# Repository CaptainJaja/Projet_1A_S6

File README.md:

# 🚀 Projet 1A S6 - Robot Bluetooth + Odometrie

Ce projet consiste à concevoir un robot télécommandé via Bluetooth grâce à une application Android, avec odométrie, détection d'obstacles, et supervision ROS.

---

## 📌 Cahier des charges

### 🔹 Robot
- Communication **UART** avec le module **Bluetooth HC-05**  
- **Contrôle de deux moteurs DC à encodeurs** via un driver **TB6612FNG**  
- **Lecture des encodeurs** pour faire de l'**odométrie**  
- **Connexion à une Raspberry Pi** pour supervision et traitement via **ROS**  
- **Détection d'obstacle** via un capteur **ultrason HC-SR04**  
- **Module infrarouge** pour détection de ligne ou d'obstacles courts  
- **Affichage LED** pour état du robot ou esthétique  
- **Commande de deux servo-moteurs** pour actionner des éléments  

### 🔹 Application Android
- Interface graphique avec **boutons de commande**  
- **Connexion Bluetooth** pour envoyer des commandes au robot  

---

## ⚙️ Matériel utilisé

| Composant | Référence | Rôle |
|-----------|-----------|-----------|
| **Microcontrôleur** | STM32 (modèle à préciser) | Gestion des moteurs, capteurs, servo et communication Bluetooth |
| **Module Bluetooth** | HC-06 / HC-05 | Communication avec l’application Android |
| **Moteurs DC à encodeur** | GA12-N20 + encodeur magnétique | Déplacement du robot + odométrie |
| **Driver moteur** | TB6612FNG | Pilotage des moteurs |
| **Batterie** | LiPo 7.4V (capacité à préciser) | Alimentation du système |
| **Régulateurs de tension** | 7.4V → 5V (R-78B5.0-2.0), 5V → 3.3V (BU33SD5WG-TR)| Alimentation des composants |
| **Capteur ultrason** | HC-SR04 | Détection d'obstacles |
| **Module infrarouge** | (modèle à préciser) | Détection de ligne ou d'obstacle proche |
| **Servomoteurs** | (modèle à préciser) x2 | Actionneurs divers |
| **LEDs** | 2x minimum | Indicateurs visuels |
| **Raspberry Pi** | (modèle à préciser) | Exécution de ROS et traitement haut niveau |

---

## 🛠 Architecture du PCB

Notre projet comporte **deux versions de PCB** :

### V1 : Prototype de base
- Connecteurs moteurs, servo, HC-SR04, HC-05 ; Driver ; STM
- Pas d'encodeur, ni module infrarouge, ni connecteurs pour la Raspberry Pi

### V2 : Version finale
- Connecteurs pour les **encodeurs**, la **Raspberry Pi**, et le **module infrarouge** ajoutés
- Circuits d'alimentation optimisés pour alimentation partagée

---

## ⏳ Tableau d'avancement du projet

| Séance | Avancement                                                                                                                                                                                                           |
|--------|----------------------------------------------------------------------------------------------------------------------------------------------------------------------------------------------------------------------|
| Séance 1 | Répartition des tâches (modélisation 3D / code + PCB / appli Android), choix des composants                                                                                                                          |
| Séance 2 | - Début du PCB V1 (sans encodeur, Raspberry, infrarouge) <br>- Début application Android <br>- Début modélisation mécanique                                                                                          |
| Séance 3 | - Finalisation du PCB V1 <br>- 1ère version de l'application (nombreuses fonctionnalités manquantes)<br>-la conception 3D continue d'avancer                                                                         |
| Séance 4 | - Début des tests du **module HC-05** <br>- Implémentation des fonctionnalités mais beaucoup d'erreurs <br>-changement des dimensions de la structure 3D car changement d'agencement des éléments dans le robot |
| Séance 5 | Finalisation de la **commande à distance** (prototype robot avec HC-05)<br>-la conception 3D continue d'avancer                                                                                                      |
| Séance 6 | - Début du PCB V2 (ajout Raspberry, encodeurs, infrarouge) <br>- Plus d'erreurs grâce aux bonnes permissions demandées <br>- début de l'impression 3D                                                                |
| Séance 7 | Finalisation du modèle du PCB V2, **commande des composants et du PCB** <br>-fin de l'impression 3D                                                                                                                  |
| Séance 8 | Finalisation du modèle 3D, montage PCB et robot prototype, test |
| Séance 9 | Corrections et impressions 3D, montage du robot final |
---

## 📋 Répartition des tâches

| Nom | Tâche principale                                                                                                                                                       |
|-----------|------------------------------------------------------------------------------------------------------------------------------------------------------------------------|
| **CAPODAGI Janus** | Conception PCB (https://github.com/CaptainJaja/Projet_1A_S6/tree/main/Hardware/PCB),  code STM32 (https://github.com/CaptainJaja/Projet_1A_S6/tree/main/Software/Code) |
| **BUI HAI Christophe** | Développement de l’application Android (https://github.com/CaptainJaja/Projet_1A_S6/tree/main/Application)                                                             |
| **MILLON Raphaëlle** | Conception mécanique du robot :modélisation 3D, intégration Raspberry (https://github.com/CaptainJaja/Projet_1A_S6/tree/main/Hardware/3D)                              |

---

## 📝 Remarques et pistes d'amélioration

- Ajouter un schéma de l'architecture du système (STM32 + Raspberry + ROS)
- Tester la communication entre STM32 et Raspberry via UART 

---

Ce README est susceptible d'être mis à jour au fur et à mesure de l'avancement du projet. 🚀

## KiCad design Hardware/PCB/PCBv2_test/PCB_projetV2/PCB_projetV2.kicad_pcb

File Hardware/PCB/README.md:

# 🚀 Robot PCB - STM32 + HC-05 + Motor Driver  

Ce projet est un PCB conçu pour contrôler un robot suiveur de ligne avec obstacle, utilisant un **STM32L552CCTx** et un module **Bluetooth HC-05** pour la communication. Il comprend un **driver moteur TB6612FNG**, plusieurs GPIO et connecteurs pour capteurs.

## 📸 Aperçu du PCB version 1 (moteur sans encodeur, pas de connexion raspberry)
### **Face Avant**

### **Face Arrière**

## 📸 Aperçu du PCB version 2 (+moteur avec encodeur, +connexion raspberry (UART), +Module infrarouge)
### **Face Avant**

### **Face Arrière**

## 📦 Composants intégrés (version finale : V2)
- **Microcontrôleur :** STM32L552CCTx
- **Communication (PinHeader 01x04) :** HC-05 (Bluetooth, connecté en UART au MCU)
- **Contrôle des moteurs :** TB6612FNG (Driver moteur DC)
- **Indicateur d'état Bluetooth :** LED
- **Interface GPIO :** Rangée **3x4 pinheader** (GPIO-3.3V-GND)
- **Connectique :**
  - 2x **Connecteurs JST 01x03** pour servomoteurs
  - 2x **Connecteurs JST 01x06** pour moteurs DC
  - 1x **Connecteur JST 01x06** pour module infrarouge
  - 1x **Connecteur JST 01x02** pour alimentation
  - 1x **Connecteur ST-LINK** pour programmation/debug
  - 1x **Connecteur PinHeader 01x02** pour connexion UART avec raspberry
  - 1x **Connecteur PinHeader 02x03** pour connexion avec les LEDs
  - 1x **Connecteur PinHeader 01x02** pour connecter les masses STM/Raspberry
- **Alimentation :**
  - **Régulateur 7.5V → 5V**
  - **Régulateur 5V → 3.3V**
- **Boutons poussoirs :**
  - **Reset du MCU**
- **Passifs :** Condensateurs de découplage, bobine, résistances (**SMD**)

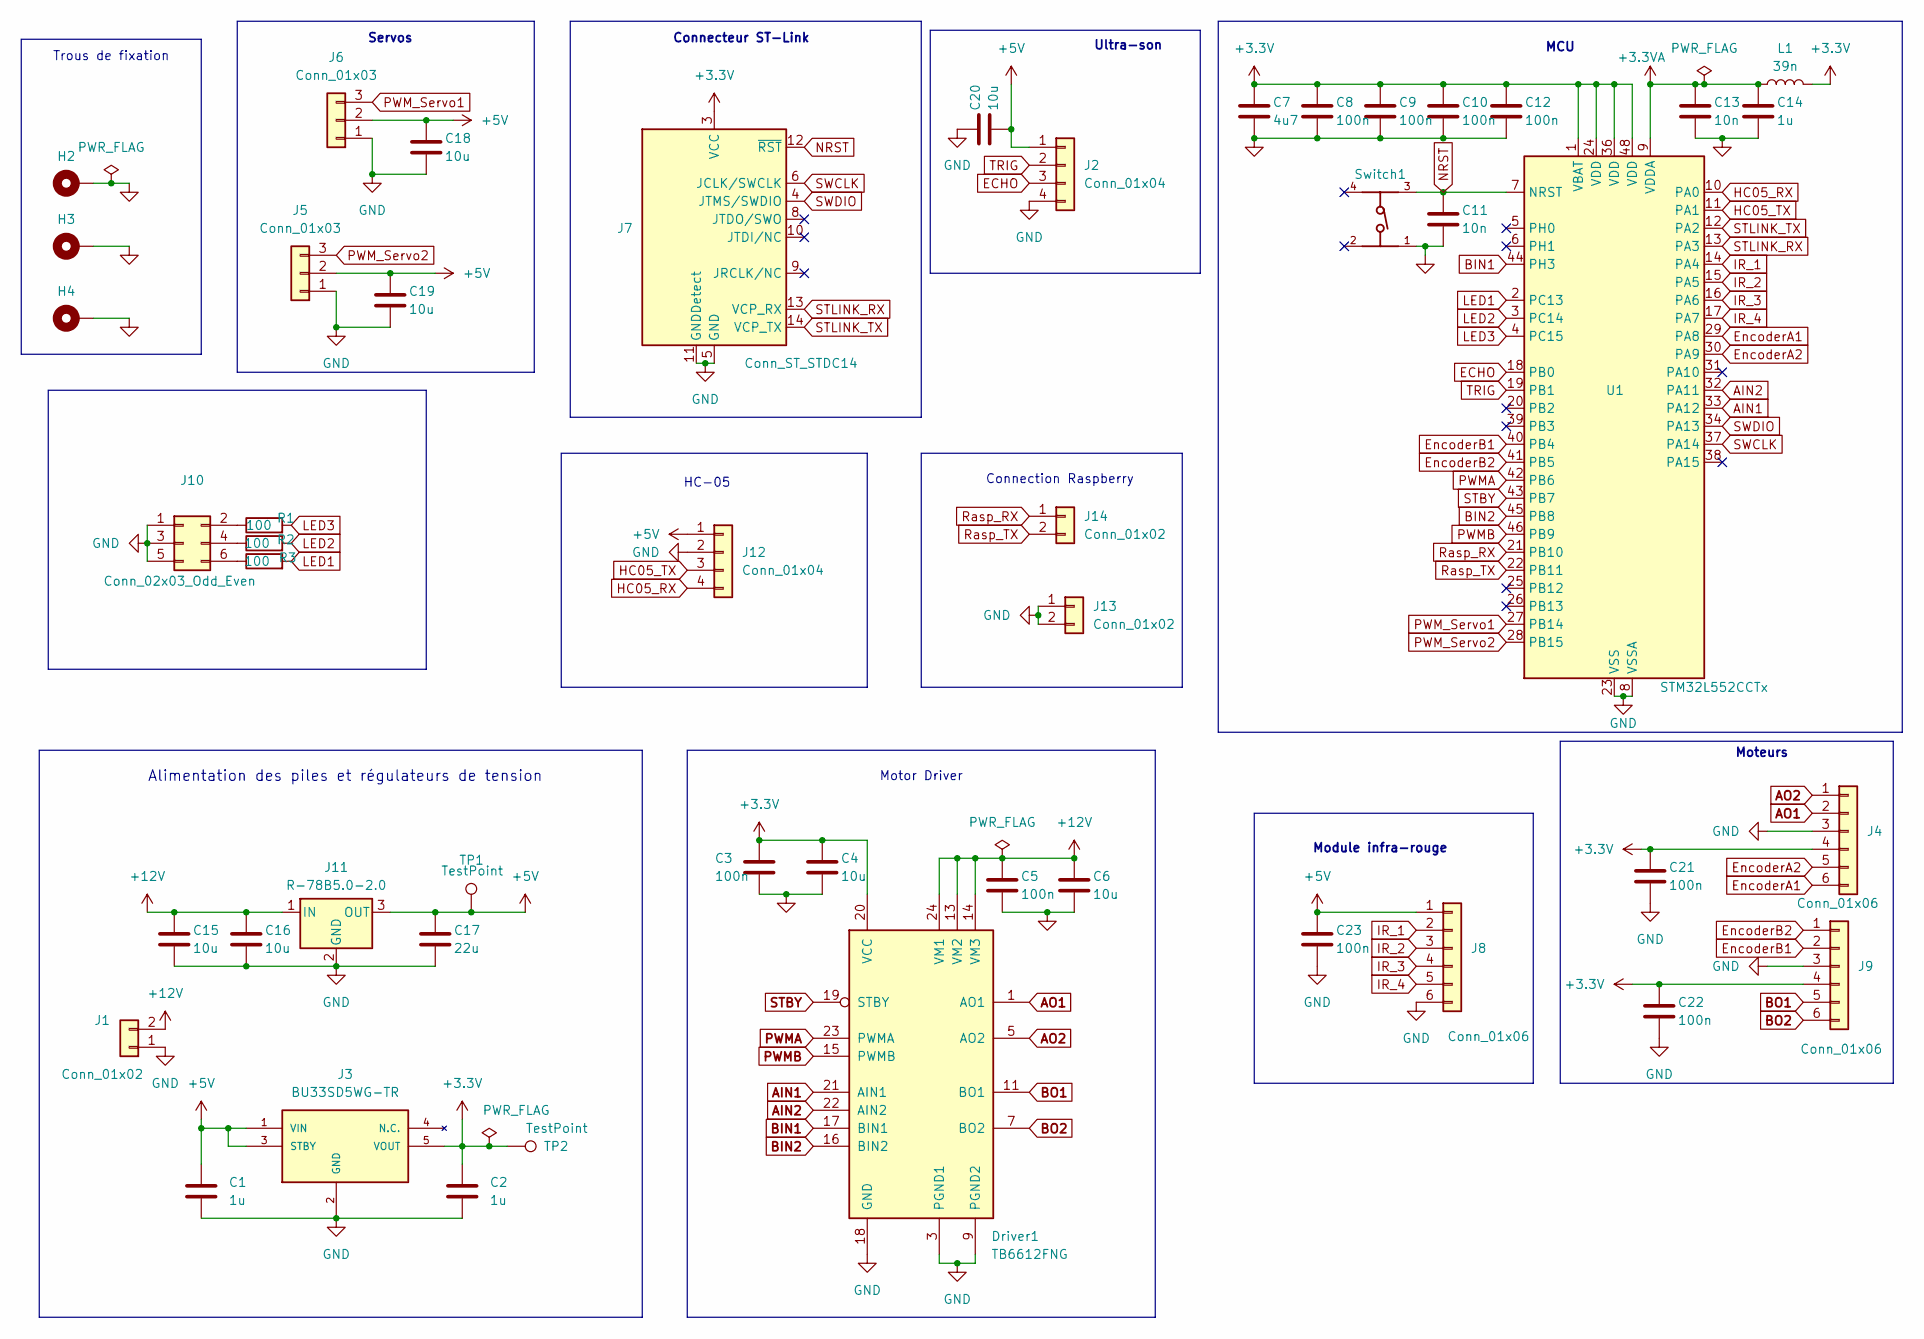
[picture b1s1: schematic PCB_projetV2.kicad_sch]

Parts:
C1, C2: 1u; C_0603_1608Metric_Pad1.08x0.95mm_HandSolder
C3, C5, C8, C9, C10, C12, C21, C22, C23: 100n; C_0402_1005Metric
C4, C6, C15, C16, C18, C19, C20: 10u; C_0603_1608Metric
C7: 4u7; C_0603_1608Metric
C11, C13: 10n; C_0402_1005Metric
C14: 1u; C_0402_1005Metric
C17: 22u; C_0805_2012Metric
Driver1: TB6612FNG; SSOP-24_5.3x8.2mm_P0.65mm
H2, H3, H4: MountingHole_Pad; MountingHole_2.7mm_M2.5_Pad
J1: Conn_01x02; JST_XH_S2B-XH-A-1_1x02_P2.50mm_Horizontal
J2: Conn_01x04; JST_PH_B4B-PH-K_1x04_P2.00mm_Vertical
J3: BU33SD5WG-TR; SOT95P280X125-5N; Mouser_Part_Number 755-BU33SD5WG-TR
J4, J9: Conn_01x06; JST_XH_B6B-XH-A_1x06_P2.50mm_Vertical
J5, J6: Conn_01x03; JST_PH_B3B-PH-K_1x03_P2.00mm_Vertical
J7: Conn_ST_STDC14; PinHeader_2x07_P1.27mm_Vertical_SMD
J8: Conn_01x06; JST_XH_S6B-XH-A-1_1x06_P2.50mm_Horizontal
J10: Conn_02x03_Odd_Even; PinSocket_2x03_P2.54mm_Vertical
J11: R-78B5.0-2.0; Converter_DCDC_RECOM_R-78B-2.0_THT
J12: Conn_01x04; PinHeader_1x04_P2.54mm_Vertical
J13: Conn_01x02; PinHeader_1x02_P2.54mm_Vertical
J14: Conn_01x02; JST_EH_B2B-EH-A_1x02_P2.50mm_Vertical
L1: 39n; L_0603_1608Metric
R1, R2, R3: 100; R_0603_1608Metric
Switch1: 430471025826; PART-NUMBER 430471025826
TP1, TP2: TestPoint; TestPoint_Pad_D2.0mm
U1: STM32L552CCTx; LQFP-48_7x7mm_P0.5mm

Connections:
+3.3V: C2.1, C3.1, C4.1, C7.1, C8.1, C9.1, C10.1, C12.1, C21.1, C22.1, Driver1.20 (VCC), J3.5 (VOUT), J4.4, J7.3 (VCC), J9.4, L1.2, TP2.1, U1.1 (VBAT), U1.24 (VDD), U1.36 (VDD), U1.48 (VDD)
+3.3VA: C13.1, C14.1, L1.1, U1.9 (VDDA)
+5V: C1.1, C17.1, C18.1, C19.1, C20.2, C23.1, J2.1, J3.1 (VIN), J3.3 (STBY), J5.2, J6.2, J8.1, J11.3 (OUT), J12.1, TP1.1
+12V: C5.1, C6.1, C15.1, C16.1, Driver1.13 (VM2), Driver1.14 (VM3), Driver1.24 (VM1), J1.2, J11.1 (IN)
AIN1: Driver1.21 (AIN1), U1.33 (PA12)
AIN2: Driver1.22 (AIN2), U1.32 (PA11)
AO1: Driver1.1 (AO1), Driver1.2 (AO1), J4.2
AO2: Driver1.5 (AO2), Driver1.6 (AO2), J4.1
BIN1: Driver1.17 (BIN1), U1.44 (PH3)
BIN2: Driver1.16 (BIN2), U1.45 (PB8)
BO1: Driver1.11 (BO1), Driver1.12 (BO1), J9.5
BO2: Driver1.7 (BO2), Driver1.8 (BO2), J9.6
ECHO: J2.3, U1.18 (PB0)
EncoderA1: J4.6, U1.29 (PA8)
EncoderA2: J4.5, U1.30 (PA9)
EncoderB1: J9.2, U1.40 (PB4)
EncoderB2: J9.1, U1.41 (PB5)
GND: C1.2, C2.2, C3.2, C4.2, C5.2, C6.2, C7.2, C8.2, C9.2, C10.2, C11.2, C12.2, C13.2, C14.2, C15.2, C16.2, C17.2, C18.2, C19.2, C20.1, C21.2, C22.2, C23.2, Driver1.3 (PGND1), Driver1.4 (PGND1), Driver1.9 (PGND2), Driver1.10 (PGND2), Driver1.18 (GND), H2.1, H3.1, H4.1, J1.1, J2.4, J3.2 (GND), J4.3, J5.1, J6.1, J7.5 (GND), J7.7 (GND), J7.11 (GNDDetect), J8.6, J9.3, J10.1, J10.3, J10.5, J11.2 (GND), J12.2, J13.1, J13.2, Switch1.1, U1.8 (VSSA), U1.23 (VSS), U1.35 (VSS), U1.47 (VSS)
HC05_RX: J12.4, U1.10 (PA0)
HC05_TX: J12.3, U1.11 (PA1)
IR_1: J8.2, U1.14 (PA4)
IR_2: J8.3, U1.15 (PA5)
IR_3: J8.4, U1.16 (PA6)
IR_4: J8.5, U1.17 (PA7)
LED1: R3.2, U1.2 (PC13)
LED2: R2.2, U1.3 (PC14)
LED3: R1.2, U1.4 (PC15)
NRST: C11.1, J7.12 (~RST), Switch1.3, U1.7 (NRST)
unnamed: J10.2, R1.1
unnamed: J10.4, R2.1
unnamed: J10.6, R3.1
PWMA: Driver1.23 (PWMA), U1.42 (PB6)
PWMB: Driver1.15 (PWMB), U1.46 (PB9)
PWM_Servo1: J6.3, U1.27 (PB14)
PWM_Servo2: J5.3, U1.28 (PB15)
Rasp_RX: J14.1, U1.21 (PB10)
Rasp_TX: J14.2, U1.22 (PB11)
STBY: Driver1.19 (STBY), U1.43 (PB7)
STLINK_RX: J7.13 (VCP_RX), U1.13 (PA3)
STLINK_TX: J7.14 (VCP_TX), U1.12 (PA2)
SWCLK: J7.6 (JCLK/SWCLK), U1.37 (PA14)
SWDIO: J7.4 (JTMS/SWDIO), U1.34 (PA13)
TRIG: J2.2, U1.19 (PB1)

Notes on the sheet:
Module infra-rouge
Alimentation des piles et régulateurs de tension
Trous de fixation
Connection Raspberry
HC-05
Moteurs
Servos
Motor Driver
MCU
Ultra-son
Connecteur ST-Link

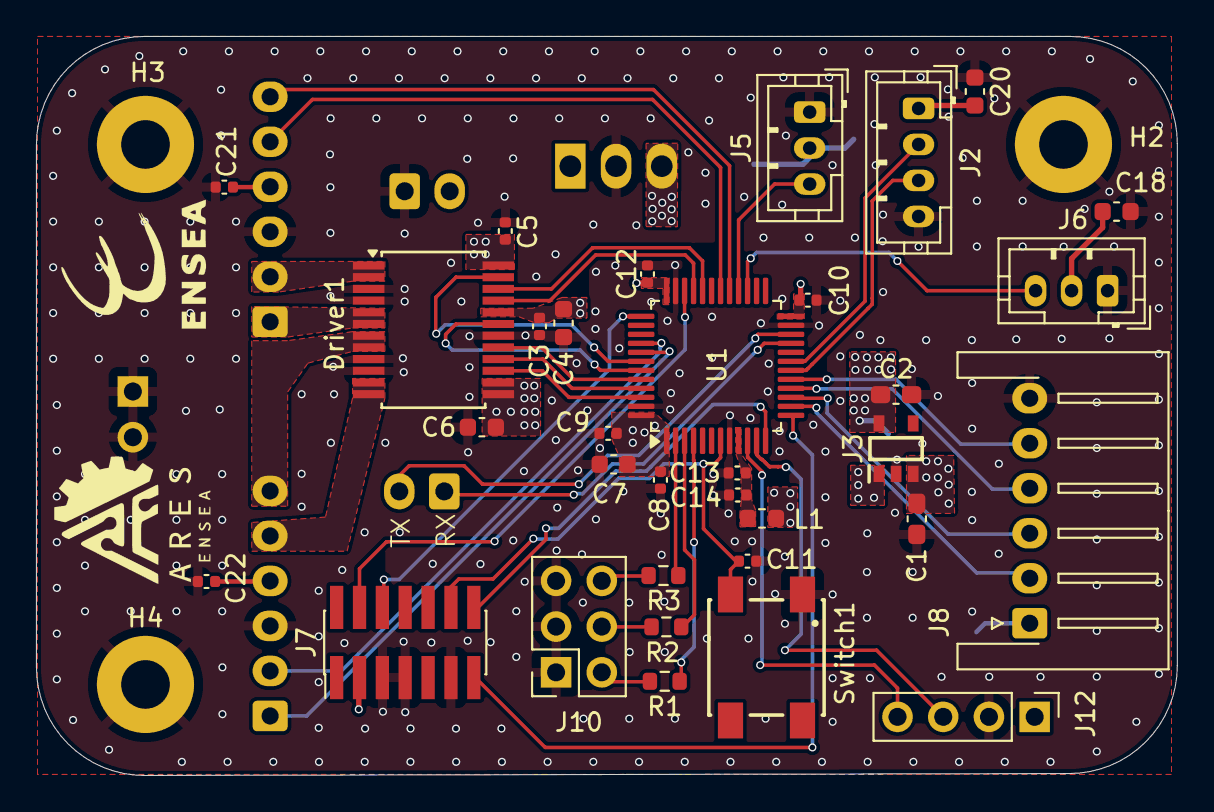
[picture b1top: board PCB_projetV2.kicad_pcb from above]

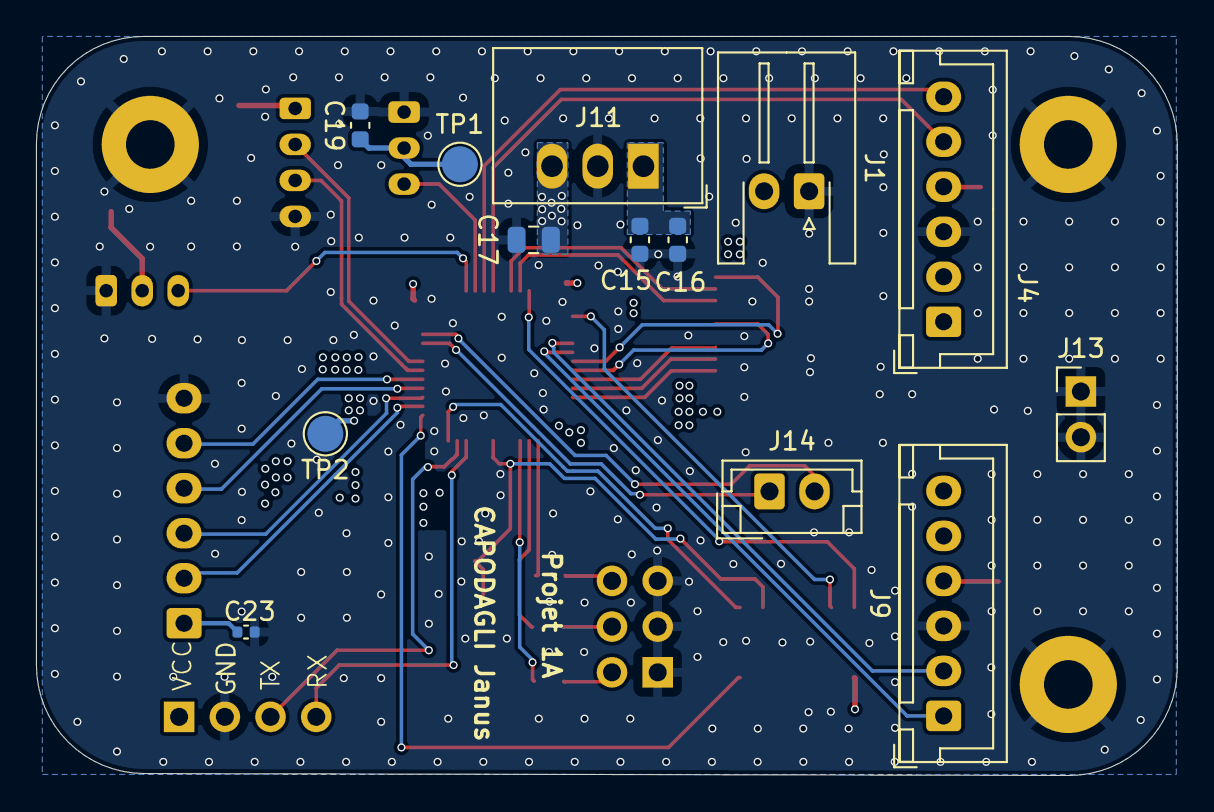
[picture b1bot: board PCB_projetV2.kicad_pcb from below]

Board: 4 copper layers, 63.4 x 41.1 mm, 49 parts (13 on the bottom side), 43 nets.

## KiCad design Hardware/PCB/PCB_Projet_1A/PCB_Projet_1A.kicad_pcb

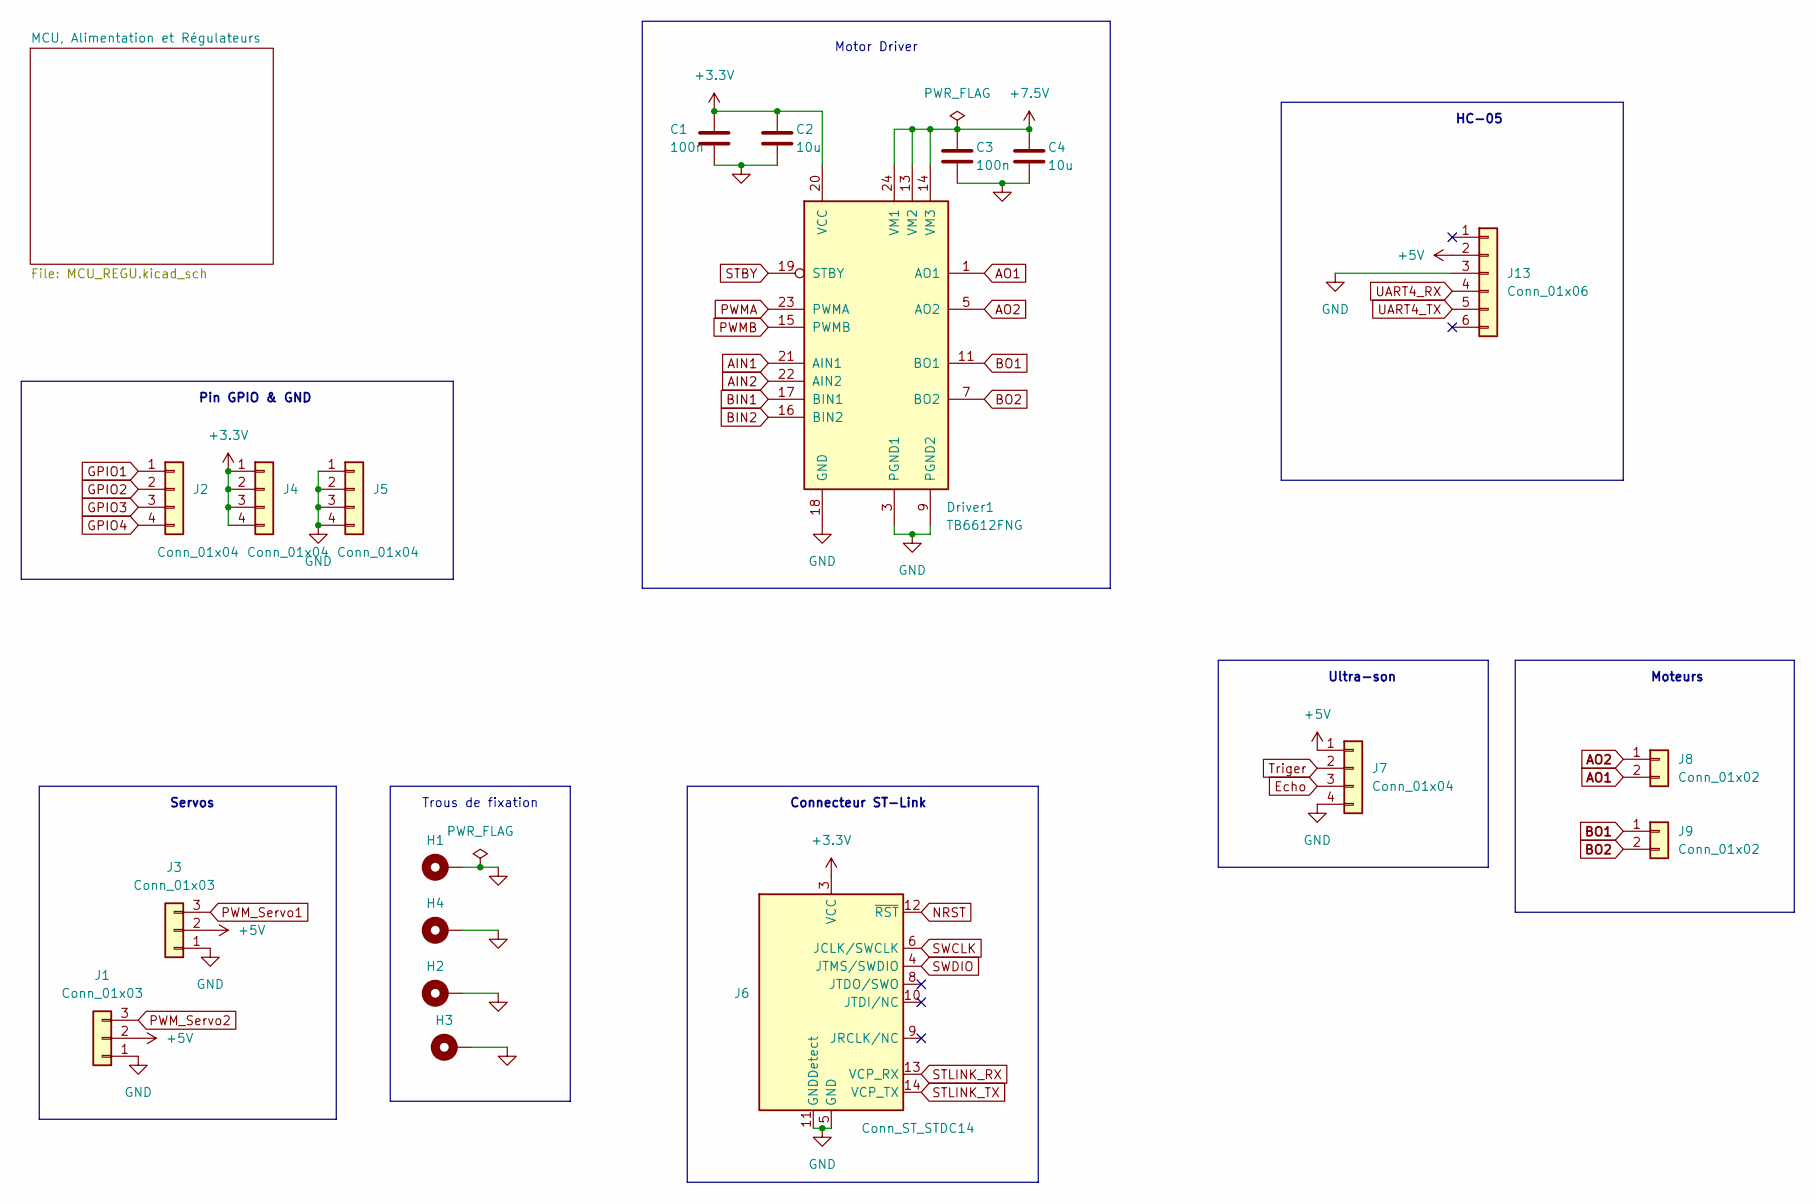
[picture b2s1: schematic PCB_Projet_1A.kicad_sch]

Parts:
C1, C3: 100n; C_0402_1005Metric
C2, C4: 10u; C_0805_2012Metric
Driver1: TB6612FNG; SSOP-24_5.3x8.2mm_P0.65mm
H1, H2, H3, H4: MountingHole_Pad; MountingHole_2.7mm_M2.5_Pad
J1, J3: Conn_01x03; JST_XH_B3B-XH-A_1x03_P2.50mm_Vertical
J2, J4, J5: Conn_01x04; PinHeader_1x04_P2.54mm_Vertical
J6: Conn_ST_STDC14; PinHeader_2x07_P1.27mm_Vertical_SMD
J7: Conn_01x04; JST_PH_B4B-PH-K_1x04_P2.00mm_Vertical
J8, J9: Conn_01x02; JST_XH_B2B-XH-A_1x02_P2.50mm_Vertical
J13: Conn_01x06; PinHeader_1x06_P2.54mm_Vertical

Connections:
+3.3V: C1.1, C2.1, Driver1.20 (VCC), J4.1, J4.2, J4.3, J4.4, J6.3 (VCC); also elsewhere on the board
+5V: J1.2, J3.2, J7.1, J13.2; also elsewhere on the board
+7.5V: C3.1, C4.1, Driver1.13 (VM2), Driver1.14 (VM3), Driver1.24 (VM1); also elsewhere on the board
AIN1: Driver1.21 (AIN1); also elsewhere on the board
AIN2: Driver1.22 (AIN2); also elsewhere on the board
AO1: Driver1.1 (AO1), Driver1.2 (AO1), J8.2
AO2: Driver1.5 (AO2), Driver1.6 (AO2), J8.1
BIN1: Driver1.17 (BIN1); also elsewhere on the board
BIN2: Driver1.16 (BIN2); also elsewhere on the board
BO1: Driver1.11 (BO1), Driver1.12 (BO1), J9.1
BO2: Driver1.7 (BO2), Driver1.8 (BO2), J9.2
Echo: J7.3; also elsewhere on the board
GND: C1.2, C2.2, C3.2, C4.2, Driver1.3 (PGND1), Driver1.4 (PGND1), Driver1.9 (PGND2), Driver1.10 (PGND2), Driver1.18 (GND), H1.1, H2.1, H3.1, H4.1, J1.1, J3.1, J5.1, J5.2, J5.3, J5.4, J6.5 (GND), J6.7 (GND), J6.11 (GNDDetect), J7.4, J13.3; also elsewhere on the board
GPIO1: J2.1; also elsewhere on the board
GPIO2: J2.2; also elsewhere on the board
GPIO3: J2.3; also elsewhere on the board
GPIO4: J2.4; also elsewhere on the board
NRST: J6.12 (~RST)
PWMA: Driver1.23 (PWMA); also elsewhere on the board
PWMB: Driver1.15 (PWMB); also elsewhere on the board
PWM_Servo1: J3.3; also elsewhere on the board
PWM_Servo2: J1.3; also elsewhere on the board
STBY: Driver1.19 (STBY); also elsewhere on the board
STLINK_RX: J6.13 (VCP_RX); also elsewhere on the board
STLINK_TX: J6.14 (VCP_TX); also elsewhere on the board
SWCLK: J6.6 (JCLK/SWCLK); also elsewhere on the board
SWDIO: J6.4 (JTMS/SWDIO); also elsewhere on the board
Triger: J7.2; also elsewhere on the board
UART4_RX: J13.4; also elsewhere on the board
UART4_TX: J13.5; also elsewhere on the board

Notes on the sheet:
Ultra-son
Servos
Connecteur ST-Link
Trous de fixation
Moteurs
Pin GPIO & GND
HC-05
Motor Driver

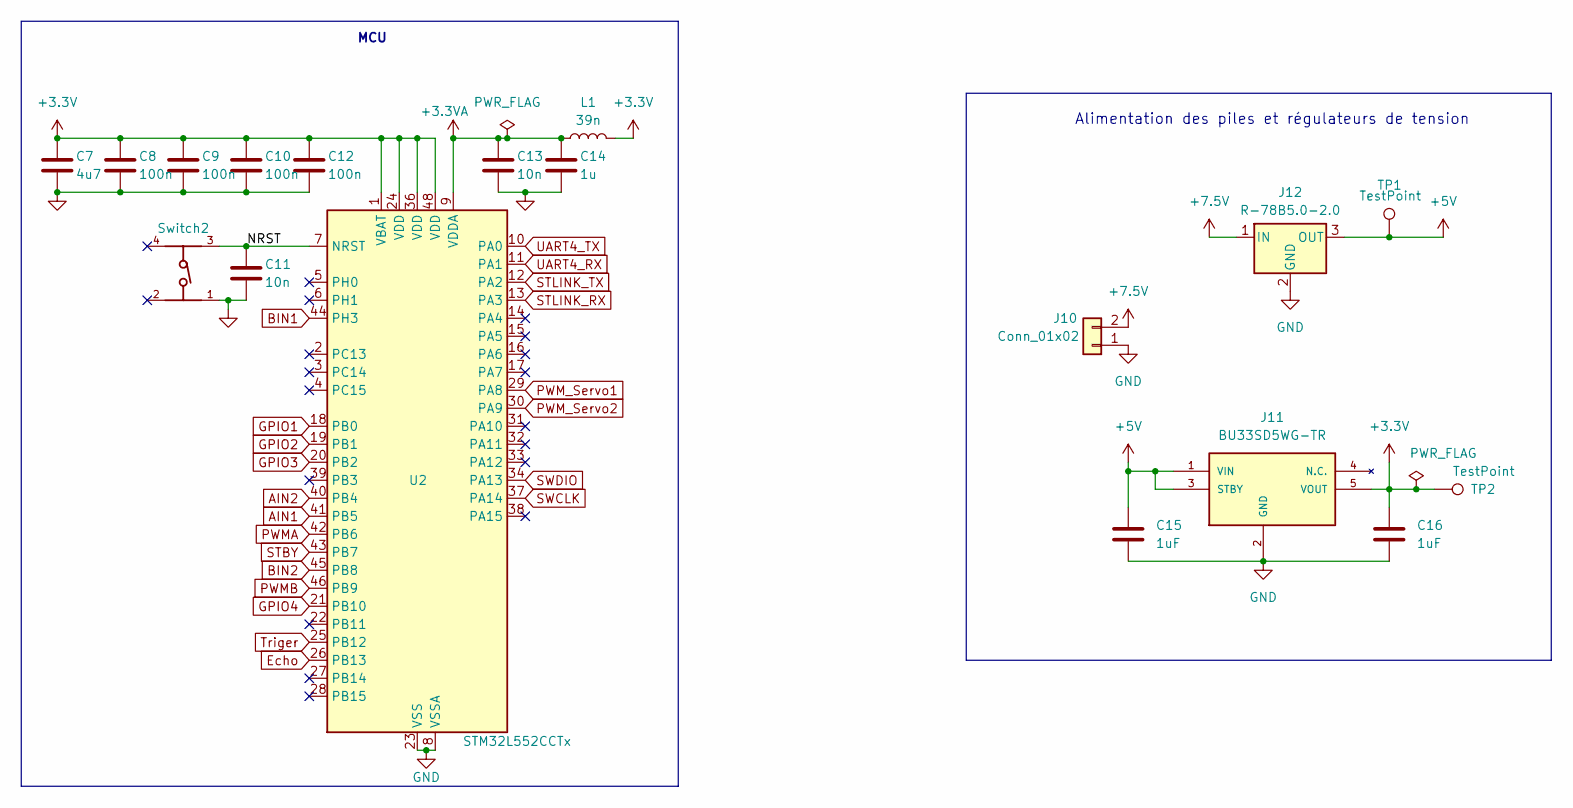
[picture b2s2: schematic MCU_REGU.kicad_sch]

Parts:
C7: 4u7; C_0805_2012Metric
C8, C9, C10, C12: 100n; C_0402_1005Metric
C11, C13: 10n; C_0402_1005Metric
C14: 1u; C_0402_1005Metric
C15, C16: 1uF; C_0603_1608Metric_Pad1.08x0.95mm_HandSolder
J10: Conn_01x02; JST_XH_B2B-XH-A_1x02_P2.50mm_Vertical
J11: BU33SD5WG-TR; SOT95P280X125-5N; Mouser_Part_Number 755-BU33SD5WG-TR
J12: R-78B5.0-2.0; Converter_DCDC_RECOM_R-78B-2.0_THT
L1: 39n; L_0603_1608Metric
Switch2: 430471025826; PART-NUMBER 430471025826
TP1, TP2: TestPoint; TestPoint_Pad_D2.0mm
U2: STM32L552CCTx; LQFP-48_7x7mm_P0.5mm

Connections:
+3.3V: C7.1, C8.1, C9.1, C10.1, C12.1, C16.1, J11.5 (VOUT), L1.2, TP2.1, U2.1 (VBAT), U2.24 (VDD), U2.36 (VDD), U2.48 (VDD); also elsewhere on the board
+3.3VA: C13.1, C14.1, L1.1, U2.9 (VDDA)
+5V: C15.1, J11.1 (VIN), J11.3 (STBY), J12.3 (OUT), TP1.1; also elsewhere on the board
+7.5V: J10.2, J12.1 (IN); also elsewhere on the board
/MCU, Alimentation et Régulateurs/NRST: C11.1, Switch2.3, U2.7 (NRST)
AIN1: U2.41 (PB5); also elsewhere on the board
AIN2: U2.40 (PB4); also elsewhere on the board
BIN1: U2.44 (PH3); also elsewhere on the board
BIN2: U2.45 (PB8); also elsewhere on the board
Echo: U2.26 (PB13); also elsewhere on the board
GND: C7.2, C8.2, C9.2, C10.2, C11.2, C12.2, C13.2, C14.2, C15.2, C16.2, J10.1, J11.2 (GND), J12.2 (GND), Switch2.1, U2.8 (VSSA), U2.23 (VSS), U2.35 (VSS), U2.47 (VSS); also elsewhere on the board
GPIO1: U2.18 (PB0); also elsewhere on the board
GPIO2: U2.19 (PB1); also elsewhere on the board
GPIO3: U2.20 (PB2); also elsewhere on the board
GPIO4: U2.21 (PB10); also elsewhere on the board
PWMA: U2.42 (PB6); also elsewhere on the board
PWMB: U2.46 (PB9); also elsewhere on the board
PWM_Servo1: U2.29 (PA8); also elsewhere on the board
PWM_Servo2: U2.30 (PA9); also elsewhere on the board
STBY: U2.43 (PB7); also elsewhere on the board
STLINK_RX: U2.13 (PA3); also elsewhere on the board
STLINK_TX: U2.12 (PA2); also elsewhere on the board
SWCLK: U2.37 (PA14); also elsewhere on the board
SWDIO: U2.34 (PA13); also elsewhere on the board
Triger: U2.25 (PB12); also elsewhere on the board
UART4_RX: U2.11 (PA1); also elsewhere on the board
UART4_TX: U2.10 (PA0); also elsewhere on the board

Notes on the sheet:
MCU
Alimentation des piles et régulateurs de tension

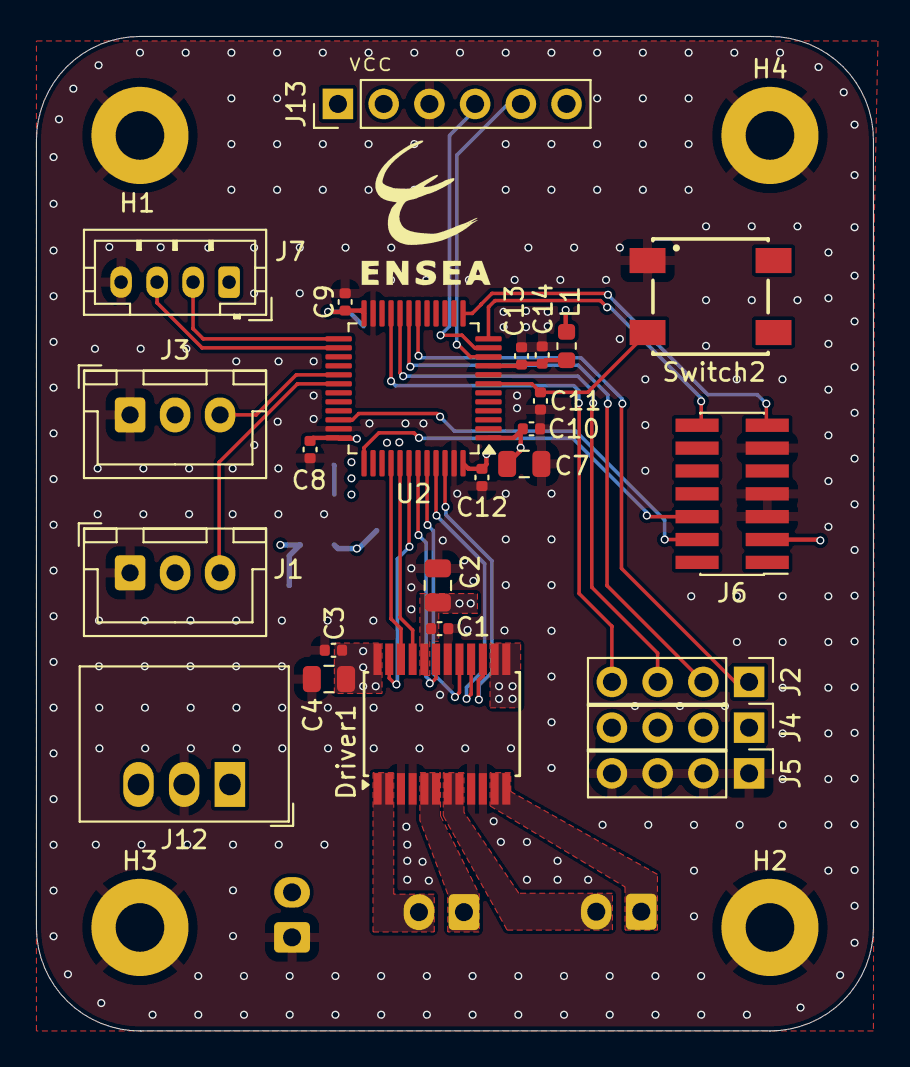
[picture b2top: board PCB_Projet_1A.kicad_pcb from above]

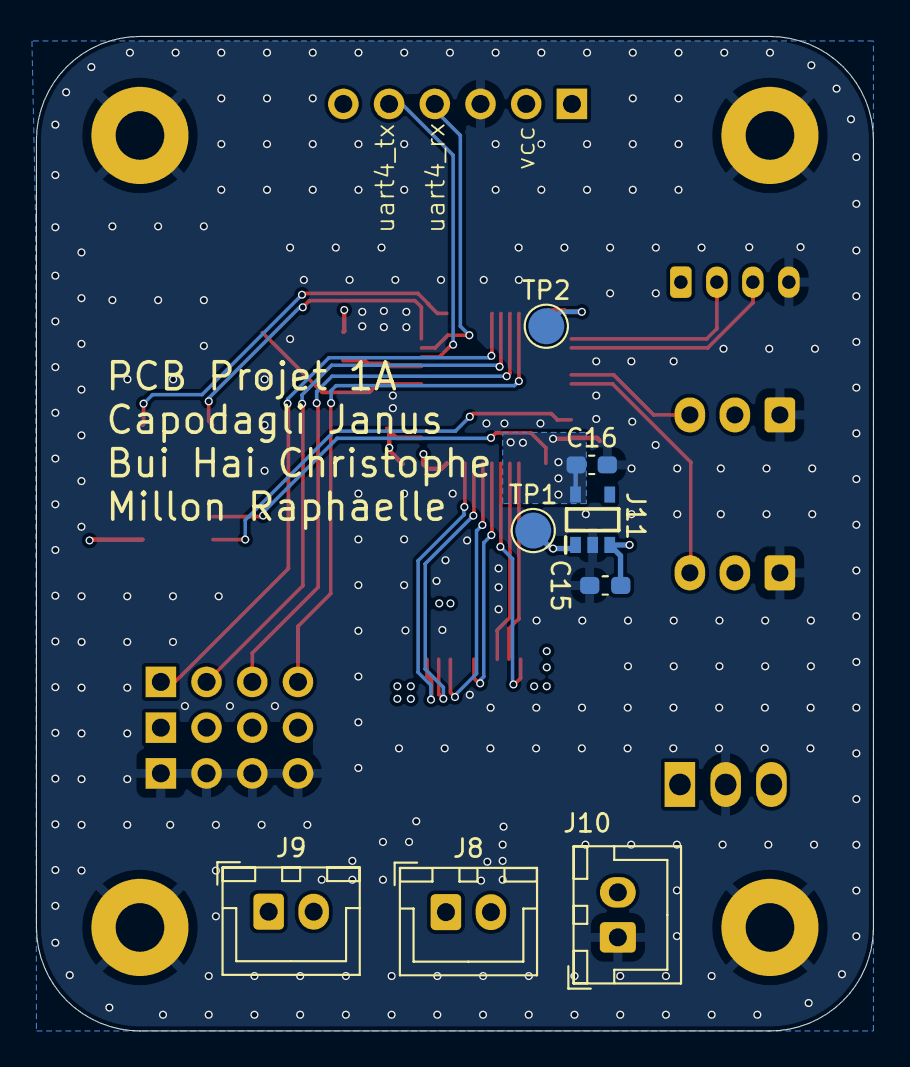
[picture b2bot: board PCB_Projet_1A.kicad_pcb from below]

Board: 4 copper layers, 46.5 x 55.2 mm, 37 parts (8 on the bottom side), 31 nets.

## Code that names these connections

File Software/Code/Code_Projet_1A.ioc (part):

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Mcu.Name=STM32L552C(C-E)Tx
Mcu.Package=LQFP48
Mcu.UserName=STM32L552CCTx
PA0.GPIOParameters=GPIO_Label
PA0.GPIO_Label=HC05_RX
PA0.Mode=Asynchronous
PA0.Signal=UART4_TX
PA1.GPIOParameters=GPIO_Label
PA1.GPIO_Label=HC05_TX
PA1.Mode=Asynchronous
PA1.Signal=UART4_RX
PA11.GPIOParameters=GPIO_Label
PA11.GPIO_Label=AIN2
PA11.Signal=GPIO_Output
PA12.GPIOParameters=GPIO_Label
PA12.GPIO_Label=AIN1
PA12.Signal=GPIO_Output
PA13\ (JTMS/SWDIO).Mode=Trace_Asynchronous_SW
PA13\ (JTMS/SWDIO).Signal=DEBUG_JTMS-SWDIO
PA14\ (JTCK/SWCLK).Mode=Trace_Asynchronous_SW
PA14\ (JTCK/SWCLK).Signal=DEBUG_JTCK-SWCLK
PA2.Mode=Asynchronous
PA2.Signal=USART2_TX
PA3.Mode=Asynchronous
PA3.Signal=USART2_RX
PA4.GPIOParameters=GPIO_Label
PA4.GPIO_Label=X1
PA4.Signal=ADCx_IN9
PA5.GPIOParameters=GPIO_Label
PA5.GPIO_Label=X2
PA5.Signal=ADCx_IN10
PA6.GPIOParameters=GPIO_Label
PA6.GPIO_Label=X3
PA6.Signal=ADCx_IN11
PA7.GPIOParameters=GPIO_Label
PA7.GPIO_Label=X4
PA7.Signal=ADCx_IN12
PA8.GPIOParameters=GPIO_Label
PA8.GPIO_Label=EncodeurA1
PA8.Signal=S_TIM1_CH1
PA9.GPIOParameters=GPIO_Label
PA9.GPIO_Label=EncodeurA2
PA9.Signal=S_TIM1_CH2
PB0.GPIOParameters=GPIO_Label
PB0.GPIO_Label=ECHO
PB0.Signal=GPXTI0
PB1.GPIOParameters=GPIO_Label
PB1.GPIO_Label=TRIG
PB1.Signal=GPIO_Output
PB10.GPIOParameters=GPIO_Label
PB10.GPIO_Label=Raspb_RX
PB10.Mode=Asynchronous
PB10.Signal=USART3_TX
PB11.GPIOParameters=GPIO_Label
PB11.GPIO_Label=Raspb_TX
PB11.Mode=Asynchronous
PB11.Signal=USART3_RX
PB14.GPIOParameters=GPIO_Label
PB14.GPIO_Label=Servo1
PB14.Signal=S_TIM15_CH1
PB15.GPIOParameters=GPIO_Label
PB15.GPIO_Label=Servo2
PB15.Signal=S_TIM15_CH2
PB3\ (JTDO/TRACESWO).Mode=Trace_Asynchronous_SW
PB3\ (JTDO/TRACESWO).Signal=DEBUG_JTDO-SWO
PB4\ (NJTRST).GPIOParameters=GPIO_Label
PB4\ (NJTRST).GPIO_Label=EncodeurB1
PB4\ (NJTRST).Signal=S_TIM3_CH1
PB5.GPIOParameters=GPIO_Label
PB5.GPIO_Label=EncodeurB2
PB5.Signal=S_TIM3_CH2
PB6.GPIOParameters=GPIO_Label
PB6.GPIO_Label=PWMA
PB6.Signal=S_TIM4_CH1
PB7.GPIOParameters=GPIO_Label
PB7.GPIO_Label=STBY
PB7.Signal=GPIO_Output
PB8.GPIOParameters=GPIO_Label
PB8.GPIO_Label=BIN2
PB8.Signal=GPIO_Output
PB9.GPIOParameters=GPIO_Label
PB9.GPIO_Label=PWMB
PB9.Signal=S_TIM4_CH4
PC13.GPIOParameters=GPIO_Label
PC13.GPIO_Label=LED1
PC13.Signal=GPIO_Output
PC14-OSC32_IN\ (PC14).GPIOParameters=GPIO_Label
PC14-OSC32_IN\ (PC14).GPIO_Label=LED2
PC14-OSC32_IN\ (PC14).Signal=GPIO_Output
PC15-OSC32_OUT\ (PC15).GPIOParameters=GPIO_Label
PC15-OSC32_OUT\ (PC15).GPIO_Label=LED3
PC15-OSC32_OUT\ (PC15).Signal=GPIO_Output
PH3-BOOT0.GPIOParameters=GPIO_Label
PH3-BOOT0.GPIO_Label=BIN1
PH3-BOOT0.Signal=GPIO_Output
RCC.HSE_VALUE=16000000
RCC.SYSCLKFreq_VALUE=80000000
RCC.SYSCLKSource=RCC_SYSCLKSOURCE_PLLCLK
board=custom

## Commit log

2025-02-06 1ere modif du README (test)
2025-02-06 modification README et ajout des répertoires
2025-02-06 ajout projet Kicad
2025-02-06 modification schematique
2025-02-06 finalisation schématique PCB
2025-02-06 Avancement sur le PCB editor
2025-02-06 Finalisation du PCB et ajout du README dans le répertoire PCB
2025-02-07 amélioration PCB : vias GND
2025-02-07 Update images du README PCB
2025-02-07 README PCB
2025-02-13 Ajout du repertoire application
2025-02-14 ajout README dans Application
2025-02-14 ajout du README dans le répertoire Test_HC05
2025-02-14 modification du README dans le répertoire Test_HC05
2025-02-14 correction README HC05
2025-02-14 Ajout du projet CubeIDE pour le robot
2025-02-14 Ajout d'un README dans le répertoire Code
2025-02-15 Modification du PCB: changement du HC05 SMD en pinheader adapté au module
2025-02-15 tentative reglage erreur commit
2025-02-15 modification de F.silkscreen et B.silkscreen et du README PCB
2025-03-06 Modification du README dans Application
2025-03-06 2eme modification de README Application
2025-03-27 Modification README
2025-03-27 Modification V2 et README
2025-04-03 modif pcb
2025-04-03 finalisation PCB v2
2025-04-03 ajout des screen shots du PCB v2 dans le répertoire PCB
2025-04-03 ajout des condensateurs pour les modules
2025-04-03 modif README
2025-04-03 amélioration finale PCB
2025-04-03 ajour gerber PCBv2
2025-04-10 MAJ PCB
2025-04-10 MAJ dossier PCB_v2
2025-04-10 Modification READ ME general
2025-04-10 Modification Application : README et V4
2025-04-10 Modification Application: README
2025-04-10 ajout répertoire 3D
2025-04-10 maj Read me
2025-04-21 MAJ PCBv2
2025-05-25 modif code
2025-05-25 suppression répertoire test_hc05
2025-05-31 Ajout de la derniere version du programme
2025-06-01 modif ioc
